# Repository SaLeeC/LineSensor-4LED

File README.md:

# LineSensor-4LED
Sensore di Linea a 4 LED

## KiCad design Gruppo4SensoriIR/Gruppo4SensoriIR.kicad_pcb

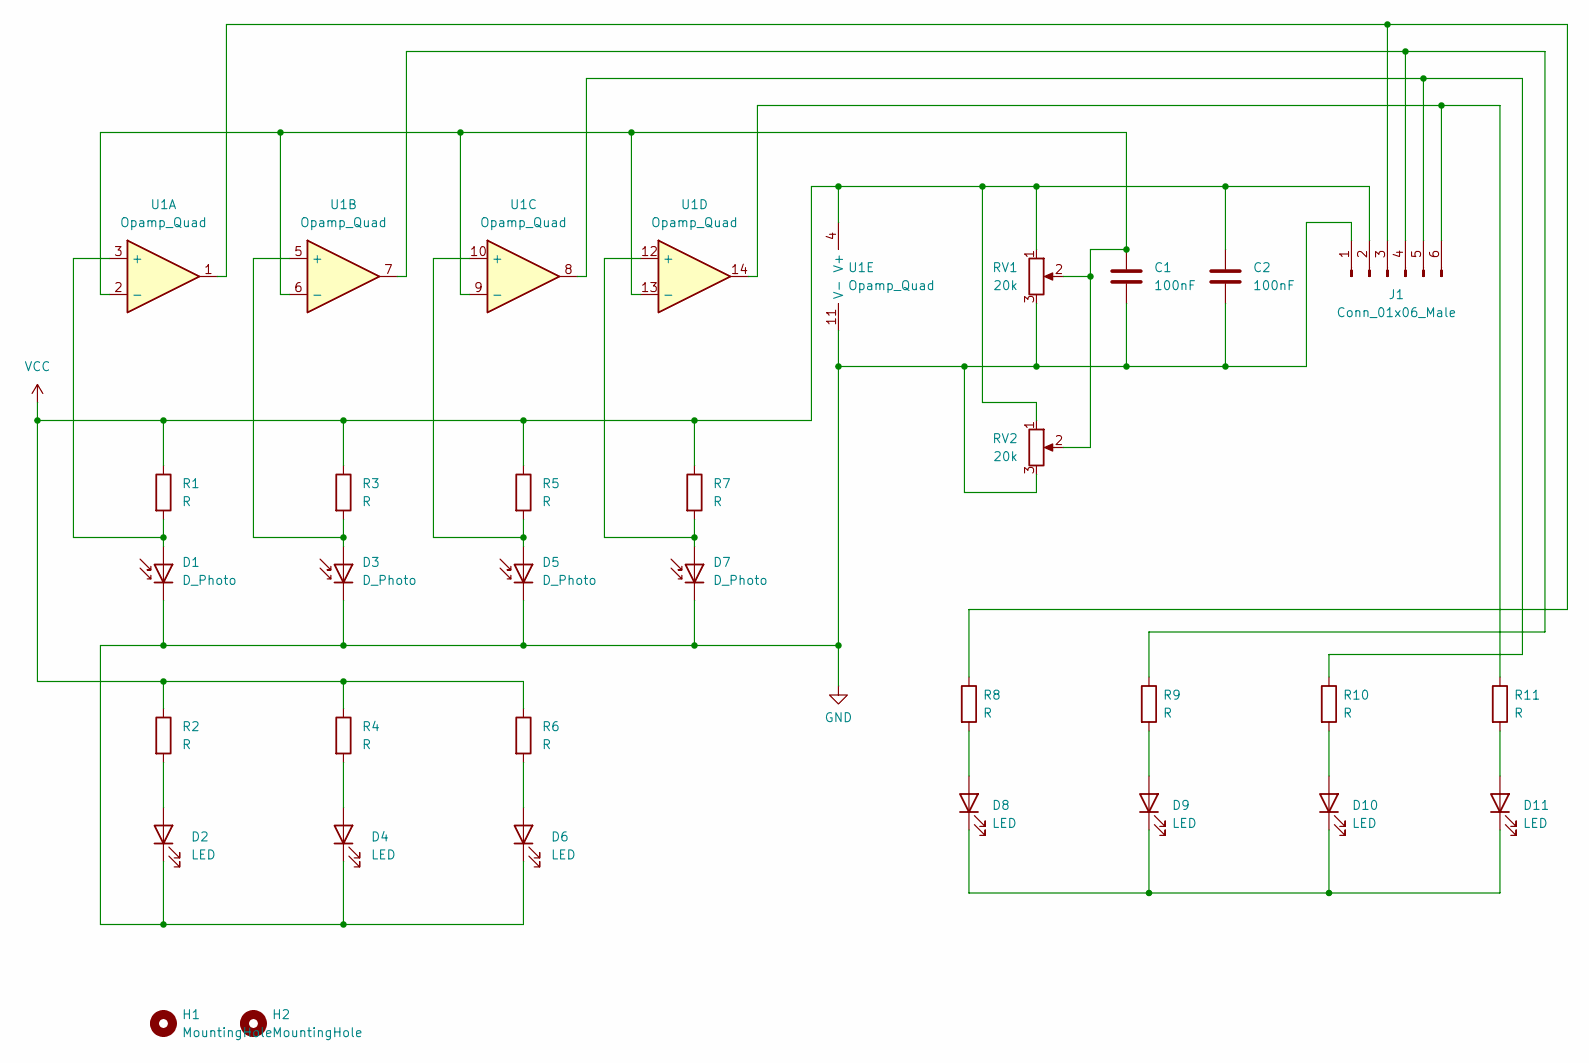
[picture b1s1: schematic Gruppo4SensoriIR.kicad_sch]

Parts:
C1, C2: 100nF; C_Axial_L3.8mm_D2.6mm_P7.50mm_Horizontal
D1, D3, D5, D7: D_Photo; LED_D5.0mm_IRBlack
D2, D4, D6: LED; LED_D5.0mm_IRGrey
D8, D9, D10, D11: LED; LED_D5.0mm
H1, H2: MountingHole; MountingHole_3.2mm_M3_DIN965_Pad
J1: Conn_01x06_Male; PinHeader_1x06_P2.54mm_Horizontal
R1, R2, R3, R4, R5, R6, R7: R; R_Axial_DIN0207_L6.3mm_D2.5mm_P2.54mm_Vertical
R8, R9, R10, R11: R; R_Axial_DIN0207_L6.3mm_D2.5mm_P10.16mm_Horizontal
RV1: 20k; Potentiometer_ACP_CA6-H2,5_Horizontal
RV2: 20k; Potentiometer_Bourns_3266Y_Vertical
U1: Opamp_Quad

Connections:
GND: C1.2, C2.2, D1.1 (K), D2.1 (K), D3.1 (K), D4.1 (K), D5.1 (K), D6.1 (K), D7.1 (K), J1.1, RV1.3, RV2.3, U1.11 (V-)
unnamed: C1.1, RV1.2, RV2.2, U1.2 (-), U1.6 (-), U1.9 (-), U1.13 (-)
unnamed: D1.2 (A), R1.2, U1.3 (+)
unnamed: D2.2 (A), R2.2
unnamed: D3.2 (A), R3.2, U1.5 (+)
unnamed: D4.2 (A), R4.2
unnamed: D5.2 (A), R5.2, U1.10 (+)
unnamed: D6.2 (A), R6.2
unnamed: D7.2 (A), R7.2, U1.12 (+)
unnamed: D9.2 (A), R9.2
unnamed: D8.1 (K), D9.1 (K), D10.1 (K), D11.1 (K)
unnamed: D10.2 (A), R10.2
unnamed: D11.2 (A), R11.2
unnamed: J1.3, R8.1, U1.1
unnamed: J1.4, R9.1, U1.7
unnamed: J1.5, R10.1, U1.8
unnamed: J1.6, R11.1, U1.14
unnamed: D8.2 (A), R8.2
VCC: C2.1, J1.2, R1.1, R2.1, R3.1, R4.1, R5.1, R6.1, R7.1, RV1.1, RV2.1, U1.4 (V+)

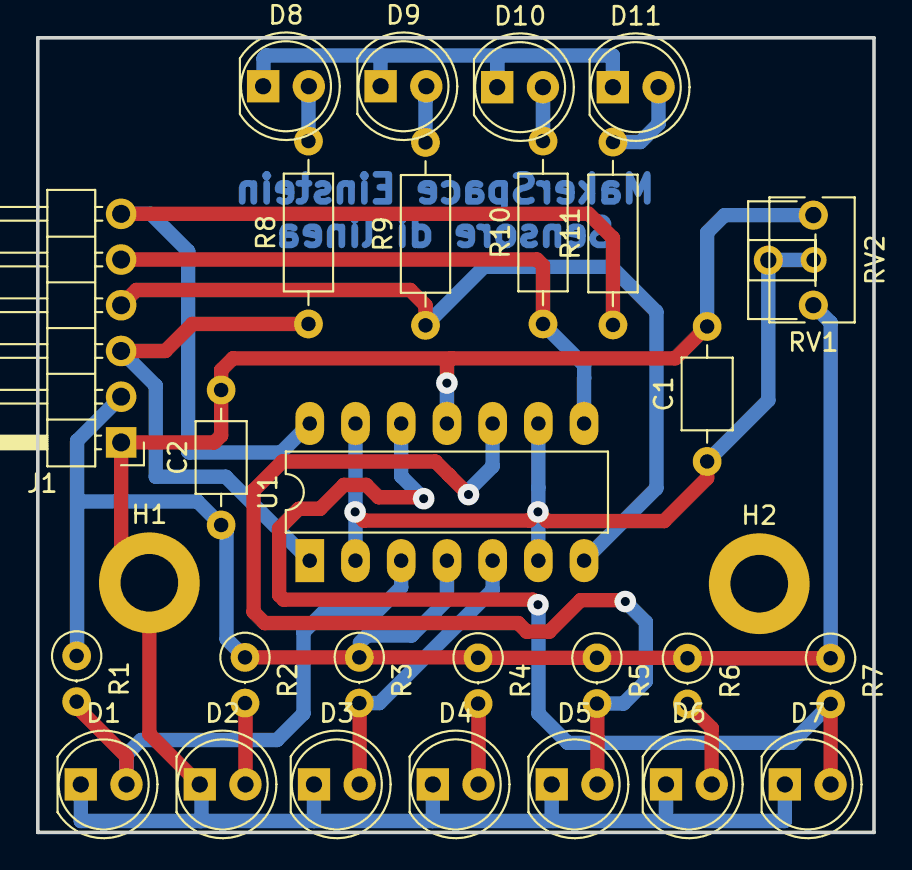
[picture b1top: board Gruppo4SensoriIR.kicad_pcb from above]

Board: 2 copper layers, 46.5 x 44.1 mm, 30 parts (0 on the bottom side), 19 nets.
